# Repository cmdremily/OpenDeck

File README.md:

# OpenDeck
An open hardware/source 32-key (4x8) macro keypad based on QMK firmware.

# What it looks like?

# BOM
- **READ THE FULL INSTRUCTIONS BEFORE ORDERING PARTS OR BEGINNING ASSEMBLY**
- 1x PCB including all components from the BOM in the `hardware` folder. It's a good idea to get some spares as it's easy to mess up the assembly.
- 32x Cherry MX RGB compatible switches (e.g. MX1A-G1NA)
- 32x Keycaps of your choice (can be 3D printed)
- 1x 3D printed case body (see `mechanical/OpenDeck32` folder)
- 1x 3D printed switch plate (see `mechanical/OpenDeck32` folder)
- 1x 3D printed front plate (see `mechanical/OpenDeck32` folder)
- 1x 3D printed stand (see `mechanical/OpenDeck32` folder)
- 4x M3x0.5 15mm flathead (countersunk) screws
- 1x USB micro-B cable

For assembly an AVR ISP (Incircuit Serial Programmer) is needed unless the DFU bootloader is already programmed and correct fuses are set on your ATmega32U4 (unlikely). If you don't have an AVR ISP, you can a make a make shift programmer from it but pay close attention to the wiring, you can destroy the OpenDeck PCB and/or your Arduino if you wire it wrong.

# Electrical Assembly
**CAUTION:** The following assembly steps require soldering of Surface Mount Devices (SMDs). If you're unfamiliar with SMD soldering I recommend viewing some tutorials on the topic and maybe purchasing a practice kit online. **DO NOT ATTEMPT ASSEMBLY IF YOU'RE NOT CONFIDENT WITH SMD SOLDERING, YOU ARE VERY LIKELY TO BREAK THE COMPONENTS**.

**CAUTION 2:** When hand soldering TQFP and SSOP chips (the two large ICs on the PCB) it is very easy to bridge the pins with solder (or flux, if you don't use a NO-CLEAN variety) and create a short circuit. This short circuit will most likely cause malfunction and could damage the chip, board or the device it's connected to, please carefully inspect and test each assembled board before powering it on. Flux should be used to make soldering easier of these components and to produce better solder joints. However note that some fluxes are electrically conductive and chemically corrosive and must be thoroughly washed off the board using isopropyl alcohol, carefull scrubbing with a toothbrush and wiping off with a tissue or disposable cloth.

## Tools needed:

- Soldering Iron with sponge or brass wool for cleaning the tip
- Thin soldering wire (much harder with thick solder but doable)
- ESD and heat safe tweezers, I recommend getting a pair of titanium tweezers
- Flux
- Isopropyl Alcohol
- Magnifying glass or microscope
- Multimeter
- AVR ISP (you can make one out of an [Arduino board and some jumper wires](https://www.arduino.cc/en/Tutorial/ArduinoISP) if you don't have one)
- Steady hands and lots of patience

## (Partial) PCB Assembly
**Note**: The crystal and two adjacent load capacitances are not strictly needed. The board will function just fine from the onboard RC oscillator of the ATmega32U4, the footprints are provided as an alternative clock source should the internal RC oscillator not be good enough.

**CAUTION**: Use an anti-static wrist band when assembling, ESD can damage the components during handling.

1. Read the full instructions before proceeding
1. Solder the ICs (ATmega32U4, IS31FL3731, USBLC6, SI2323DS) on the front side of the PCB
1. Solder the Surface Mount Device (SMD) caps, resistors, fuses and the power LED on the front of PCB, pay close attention to the orientation of any LEDs and Diodes. **DO NOT SOLDER** the RGB LEDs or the diodes of the keymatrix yet, we will verify that the assembly of the hard parts is correct befor soldering these components.
1. Good job, take a break, grab a coffee.
1. Solder the through hole components **EXCEPT** the key switches, they need to be mounted to the switch plate before soldering and the board must pass electrical testing before we solder them.
1. Solder the back side SMD components. 
1. Everything except the RGB LEDs, Switches and Diodes of the keymatrix should now be soldered.
1. Clean up the board with generous amounts of isopropyl alcohol, gentle scrubbing with a toothbrush (try to reach in between the IC legs with the bristles) and wiping off the excess with clean tissues. You can check if you have gotten all the flux residue off the board by adding more isopropyl alcohol and and scrubbing carefully but thoroughly with the toothbrush, if the isopropyl alcohol evaporates without leaving a visible stain on the PCB, it is clean (the stain is flux residue).

## Electrical Verification (Part 1)

1. Optically inspect all the pins of the ATmega32U4, IS31FL3731 and USBLC6 for solder bridges. The bridges can appear between the pad, or the legs of the IC. They can be hard to see, use good lighting and a magnifying glass or microscope to inspect.
1. Using a multimeter in resistance mode at the 100k Ohm range, put the common ground probe of the multimeter onto the ground pin on the 6 pin header and the positive probe onto VCC on the 6 pin header, you should read somewhere around 30k-60k ohm resistance initially.
   - If you read significantly lower resistance, check the board for flux residue and/or solder bridges.
   - If you read significantly higher resistance, check the board for bad solder joints and connections and if you damaged any traces during assembly.
1. Do the same thing for the power and ground pin on the USB header.
1. Turn the multimeter to continuity testing mode. Place the common ground probe on the right leg (towards the ATmega32U4) of the LED next to the ATmega32U4 and the positive probe on the other leg. The LED should light up ever so slightly if it has the correct orientation.
   - If the LED doesn't light up, test on another (not soldered) LED, if it lights up in either orientation then the one on the PCB is oriented the wrong way, desolder and reorient it properly.
1. Verify that D65 is oriented with the line on the diode facing towards the right (IMPORTANT!)
1. The board is safe to power on. 

## Firmware install

**NOTE: You're going to plug in a home made device into your potentially expensive PC, we have taken all reasonable precautions and the USB spec is fairly resilient to misbehaving devices but there is still a small risk of damage to your PC. Proceed at your own risk, you have been warned.**

**NOTE: In case there was an assembly error which we did not detect with the prior testing, the USB host controller on the connected PC may enter a fault protection mode where it shuts down the entire controller (or parts of it) this will cause devices connected to it (mice, keyboards etc) to stop working. Don't be alarmed, the controller should reset after a hard power cycle of the PC.**

1. We need to program the fuses on the chip properly, using [`avrdude`](https://www.nongnu.org/avrdude/). The fuse bits that should be burned can be passed to `avrdude` as `-U lfuse:w:0x62:m -U hfuse:w:0xd9:m -U efuse:w:0xf3:m` after having selected your ISP type, baud rate, port and the correct MCU type with `-p m32u4`.
   - TBD: Add example invocation for AVR ISP under linux
1. Download the [Atmel DFU bootloader for mega chips](http://ww1.microchip.com/downloads/en/DeviceDoc/megaUSB_DFU_Bootloaders.zip) onto your hard drive and exctract the bootloader for the ATmega32U4.
1. Using `avrdude` flash the bootloader onto the ATmega32U4. 
1. Clone https://github.com/cmdremily/qmk_firmware and `cd` into the directory.
1. [Install QMK toolbox](https://beta.docs.qmk.fm/cli/cli), we only need the DFU programmer, you can ignore warings about other programmers not being found.
   - Select the cloned repo as your `QMK_HOME`.
1. [Configure QMK toolbox](https://beta.docs.qmk.fm/cli/cli_configuration), select keyboard `opendeck/32/rev1` and keymap `default`.
1. [Compile and Flash](https://beta.docs.qmk.fm/cli/cli_commands) the built firmware onte the ATmega32U4 using the DFU (USB) bootloader/programmer.

## Electrical Verification (Part 2)

Now that the board has a firmware on it we can check that the pins driving the key matrix are not shorted.

1. Connect the PCB using USB to your PCB
1. Load up a keylogger that supports the F13 to F24 keys.
1. Using a jumper wire, we're going to short some pads on the PCB to simulate key presses. 
   - For every swich there is a left and a right through hole pad (the right slightly higher up on the PCB) and a SMD diode with two pads above it.
   - For every switch, short the right upper through hole pad to the right upper leg of the corresponding SMD diode pad, your keylogger should record a keypress as F13-F24 possibly with some modifier (shift/control).
   - Repeat for each switch to see that they are all working.
   - Pay attention to spurious key-presses or unreliable behaviour, both can indicate short circuits that need to be resolved by reflowing joints to remove bridges or by cleaning out flux residue.
 1. If all the keys work proceed to the next stage.

## (partial) PCB assembly and verification Part 2

1. Solder all the remaining SMD components. Each of the diodes and RGB diodes have an orientation that must be respected when assembling.
   - To verify that the RGB diode is correctly oriented, take your multimeter in continuity testing mode, place the positive lead on the bottom left pin of the RGB LED and the common ground lead on any other pin, you should see one of the LEDs light up slightly, if not, rotate the LED.
   - Note that the colours of the LED may not be what you expect due to the low burden voltage of the multimeter. In particular the blue may appear red. Don't worry about this for now, we only need to worry about them lighting up at all which shows us the correct orientation.
   - The diodes should have a line marking on them, this line must face the marking on the PCB (to the right).
   - The RGB diodes' legs are small and close together, they are very easy to shord, please be careful and pay close attention to the solder.
1. Follow the procedure from above to clean up any flux residue from the board.
1. Optically inspect the solder joints for shorts and bridges.
1. Plug into PC, you should now see RCB puke on the key matrix.
1. Validate that all three LEDs are working on all switches.
1. Using the same jumper and keylogger from before, short the switch legs (left and right pad of the swich now, instead of the diode) to test that each diode is oriented correctly. Doing repairs after we have soldered the switches will be extremely hard due to the switch plate not allowing access without desoldering ALL switches. **PLEASE DO NOT SKIP THIS VERIFICATION STEP**.

# Final Assembly
0. Clip all switches to the switch plate, mind the orientation of the plate and the switches with respect to the PCB
0. Attach the PCB and the switchplate with the switches, make sure that the 6 pin header next to the reset push button on the PCB is inside of the opening on the bottom of the switch plate
0. Once certain that everything is correctly attached, solder the switches from the back of the PCB
0. Place the PCB and switch plate assembly in the case body, pay close attention to the USB connector's opening
0. Add the front plate on top, pay attention to orientation and screw together the assembly from the bottom using the M3x0.5 15mm screws, note that the screws are self tapping and you will encounter some resistance. Do not screw in too fast to avoid deforming the threads.
   - Note that the front cover, switch plate and case will "sandwitch" the PCB to hold it in place and the two bottom screws will go through the mounting holes in the PCB.
0. Attach keycaps
0. Plug in.
0. Place on stand and enjoy.

# Use
The keys are programmed to send F13-F24 with various combinations of modifiers (shift + control) by default. You can modify the firmware to send different key combinations or whatever you'd please by changing the source code in `keyboards/opendeck/32/` to your liking. Instructions for that can be found in the QMK documentation. You can also set specific RGB colour per key etc.

The device will appear as a regular USB keyboard to your computer.

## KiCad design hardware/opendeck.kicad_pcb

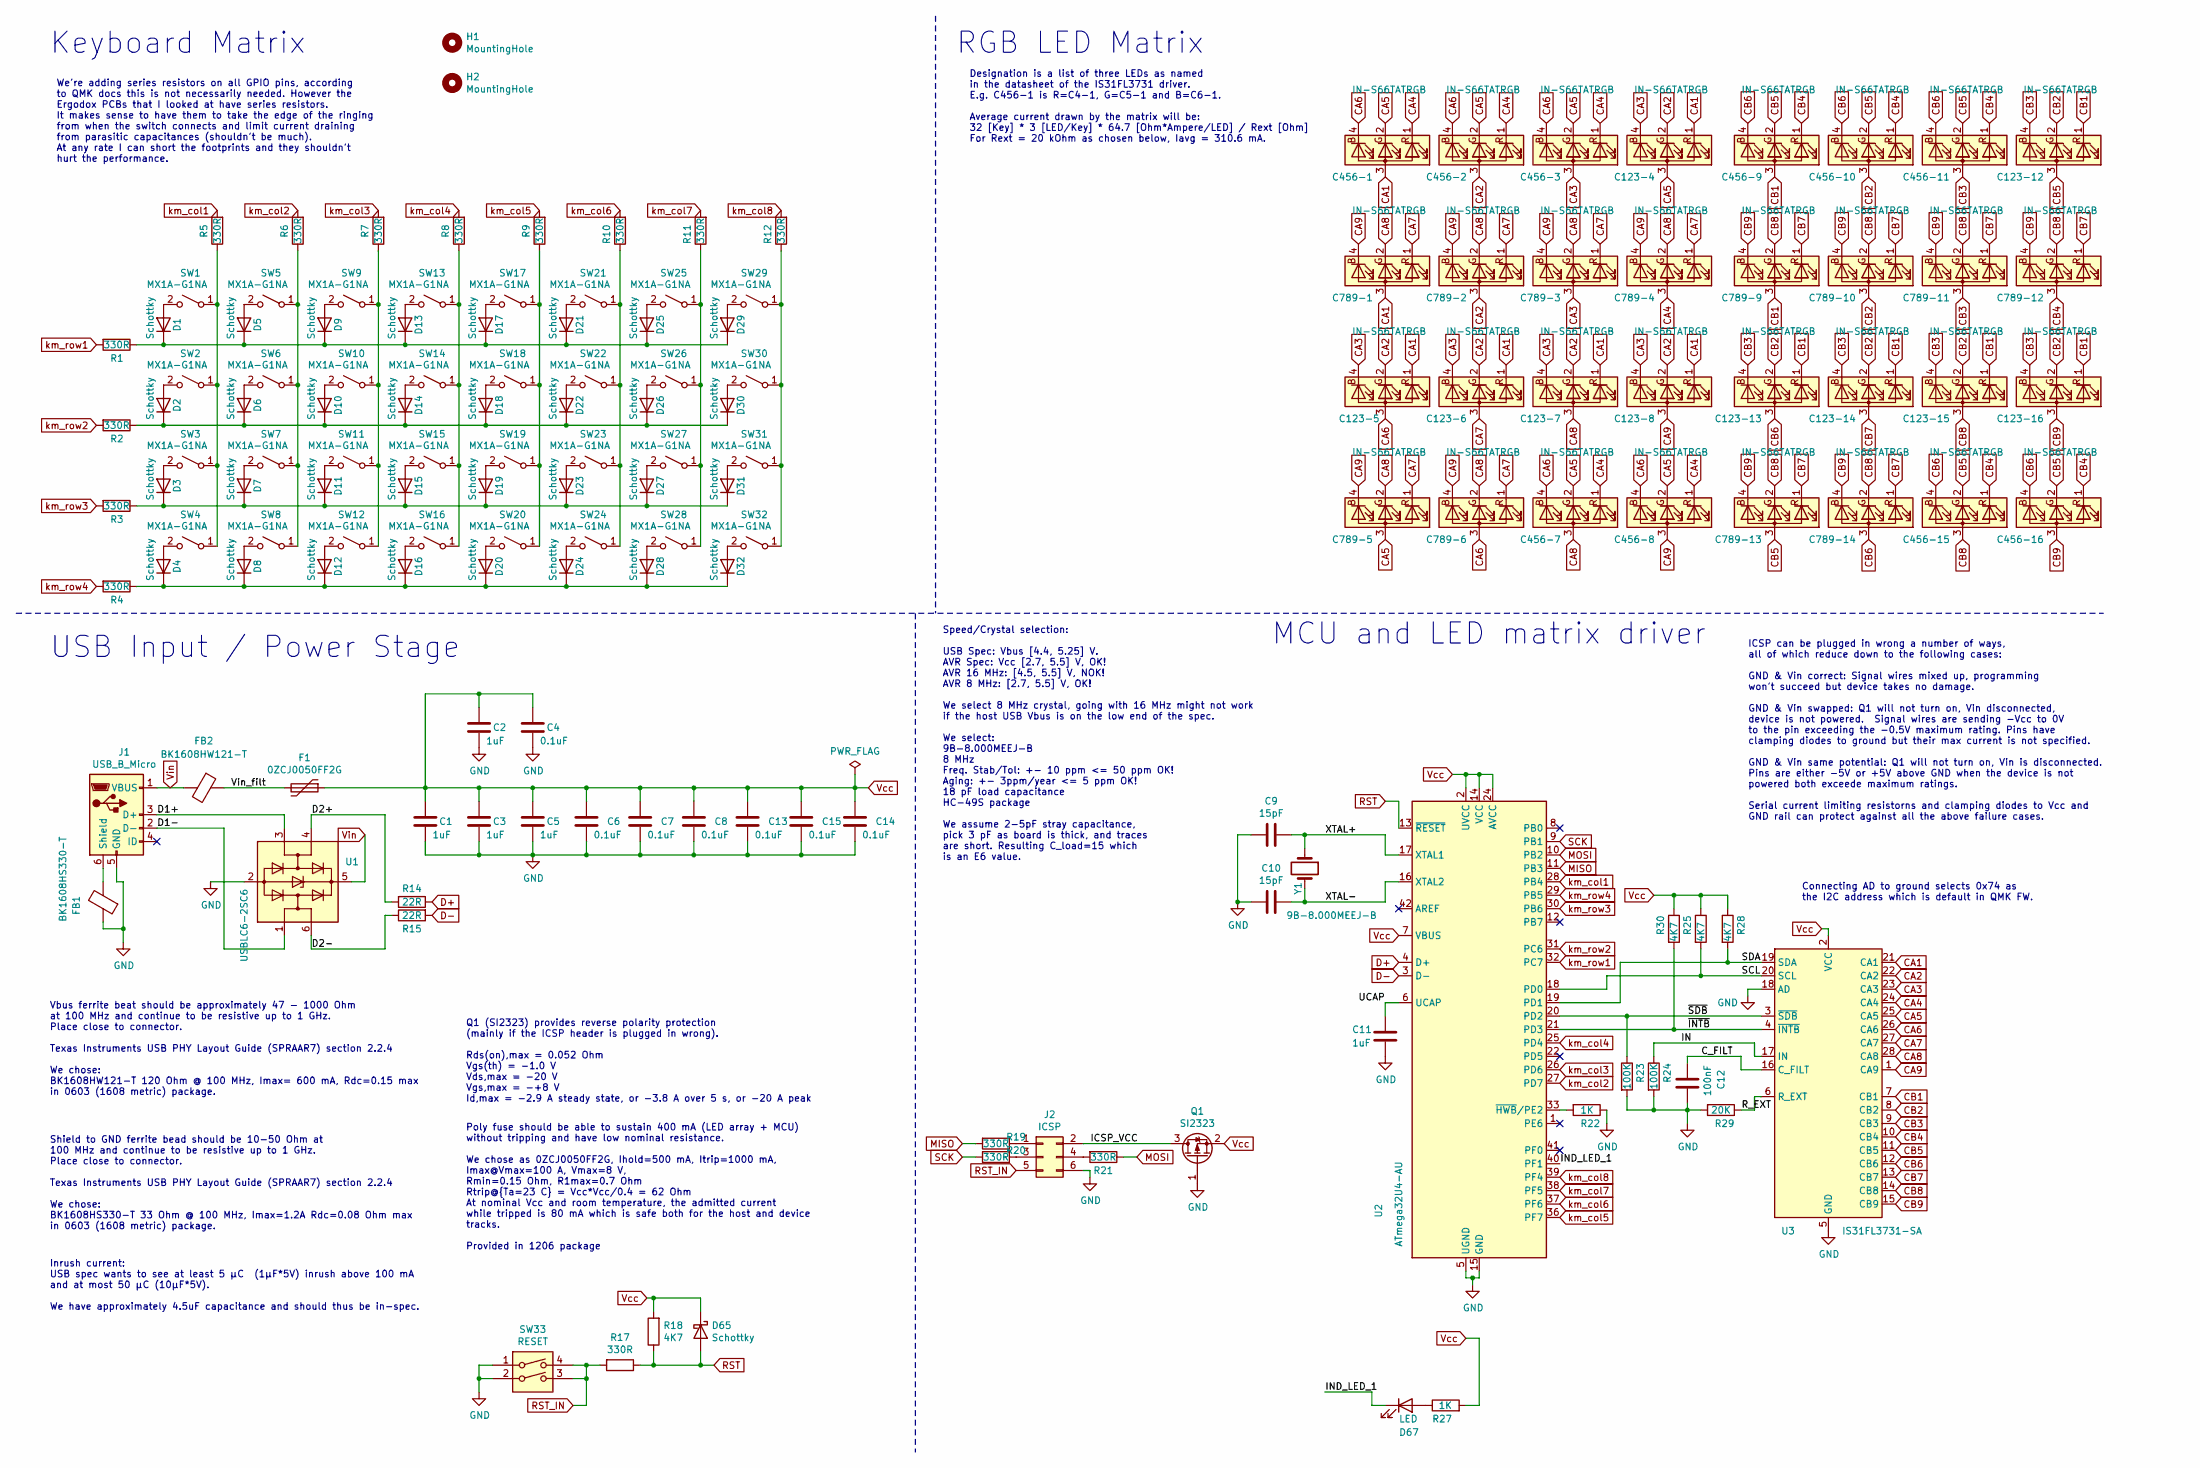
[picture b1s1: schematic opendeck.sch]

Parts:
C1, C2, C3, C5, C11: 1uF; C_0603_1608Metric
C4, C6, C7, C8, C13, C14, C15: 0.1uF; C_0603_1608Metric
C9, C10: 15pF; C_0603_1608Metric
C12: 100nF; C_0603_1608Metric
C123-4, C123-5, C123-6, C123-7, C123-8, C123-12, C123-13, C123-14, C123-15, C123-16, C456-1, C456-2, C456-3, C456-7, C456-8, C456-9, C456-10, C456-11, C456-15, C456-16, C789-1, C789-2, C789-3, C789-4, C789-5, C789-6, C789-9, C789-10, C789-11, C789-12, C789-13, C789-14: IN-S66TATRGB; RGB_LED_0606_1.6x1.5mm
D1, D2, D3, D4, D5, D6, D7, D8, D9, D10, D11, D12, D13, D14, D15, D16, D17, D18, D19, D20, D21, D22, D23, D24, D25, D26, D27, D28, D29, D30, D31, D32, D65: Schottky; D_SOD-123
D67: LED; D_0603_1608Metric
F1: 0ZCJ0050FF2G; Fuse_1206_3216Metric
FB1: BK1608HS330-T; L_0603_1608Metric
FB2: BK1608HW121-T; L_0603_1608Metric
H1, H2: MountingHole; MountingHole_4mm
J1: USB_B_Micro; USB_Micro-B_Molex-105017-0001
J2: ICSP; PinHeader_2x03_P2.54mm_Vertical
Q1: SI2323; SOT-23-Power
R1, R2, R3, R4, R5, R6, R7, R8, R9, R10, R11, R12, R17, R19, R20, R21: 330R; R_0603_1608Metric
R14, R15: 22R; R_0603_1608Metric
R18, R25, R28, R30: 4K7; R_0603_1608Metric
R22, R27: 1K; R_0603_1608Metric
R23, R24: 100K; R_0603_1608Metric
R29: 20K; R_0603_1608Metric
SW1, SW2, SW3, SW4, SW5, SW6, SW7, SW8, SW9, SW10, SW11, SW12, SW13, SW14, SW15, SW16, SW17, SW18, SW19, SW20, SW21, SW22, SW23, SW24, SW25, SW26, SW27, SW28, SW29, SW30, SW31, SW32: MX1A-G1NA; SW_Cherry_MX_1.00u_PCB
SW33: RESET; SW_TH_Tactile_Omron_B3F-10xx
U1: USBLC6-2SC6; SOT-23-6
U2: ATmega32U4-AU; TQFP-44_10x10mm_P0.8mm
U3: IS31FL3731-SA; SSOP-28_5.3x10.2mm_P0.65mm
Y1: 9B-8.000MEEJ-B; Crystal_HC49-U_Vertical

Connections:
/C_FILT: C12.1, U3.16 (C_FILT)
/D1+: J1.3 (D+), U1.3 (I/O2)
/D1-: J1.2 (D-), U1.1 (I/O1)
/D2+: R14.2, U1.4 (I/O2)
/D2-: R15.1, U1.6 (I/O1)
/ICSP_VCC: J2.2, Q1.3 (D)
/IN: R24.1, U3.17 (IN)
/IND_LED_1: D67.1 (K), U2.40 (PF1)
/R_EXT: R29.1, U3.6 (R_EXT)
/SCL: R25.2, U2.18 (PD0), U3.20 (SCL)
/SDA: R28.2, U2.19 (PD1), U3.19 (SDA)
/UCAP: C11.1, U2.6 (UCAP)
/Vin_filt: F1.2, FB2.1
/XTAL+: C9.1, U2.17 (XTAL1), Y1.1
/XTAL-: C10.1, U2.16 (XTAL2), Y1.2
/~INTB: R30.2, U2.21 (PD3), U3.4 (~INTB)
/~SDB: R23.1, U2.20 (PD2), U3.3 (~SDB)
CA1: C123-4.1, C123-5.1, C123-6.1, C123-7.1, C123-8.1, C456-1.3, C789-1.3, U3.21 (CA1)
CA2: C123-4.2, C123-5.2, C123-6.2, C123-7.2, C123-8.2, C456-2.3, C789-2.3, U3.22 (CA2)
CA3: C123-4.4, C123-5.4, C123-6.4, C123-7.4, C123-8.4, C456-3.3, C789-3.3, U3.23 (CA3)
CA4: C456-1.1, C456-2.1, C456-3.1, C456-7.1, C456-8.1, C789-4.3, U3.24 (CA4)
CA5: C123-4.3, C456-1.2, C456-2.2, C456-3.2, C456-7.2, C456-8.2, C789-5.3, U3.25 (CA5)
CA6: C123-5.3, C456-1.4, C456-2.4, C456-3.4, C456-7.4, C456-8.4, C789-6.3, U3.26 (CA6)
CA7: C123-6.3, C789-1.1, C789-2.1, C789-3.1, C789-4.1, C789-5.1, C789-6.1, U3.27 (CA7)
CA8: C123-7.3, C456-7.3, C789-1.2, C789-2.2, C789-3.2, C789-4.2, C789-5.2, C789-6.2, U3.28 (CA8)
CA9: C123-8.3, C456-8.3, C789-1.4, C789-2.4, C789-3.4, C789-4.4, C789-5.4, C789-6.4, U3.1 (CA9)
CB1: C123-12.1, C123-13.1, C123-14.1, C123-15.1, C123-16.1, C456-9.3, C789-9.3, U3.7 (CB1)
CB2: C123-12.2, C123-13.2, C123-14.2, C123-15.2, C123-16.2, C456-10.3, C789-10.3, U3.8 (CB2)
CB3: C123-12.4, C123-13.4, C123-14.4, C123-15.4, C123-16.4, C456-11.3, C789-11.3, U3.9 (CB3)
CB4: C456-9.1, C456-10.1, C456-11.1, C456-15.1, C456-16.1, C789-12.3, U3.10 (CB4)
CB5: C123-12.3, C456-9.2, C456-10.2, C456-11.2, C456-15.2, C456-16.2, C789-13.3, U3.11 (CB5)
CB6: C123-13.3, C456-9.4, C456-10.4, C456-11.4, C456-15.4, C456-16.4, C789-14.3, U3.12 (CB6)
CB7: C123-14.3, C789-9.1, C789-10.1, C789-11.1, C789-12.1, C789-13.1, C789-14.1, U3.13 (CB7)
CB8: C123-15.3, C456-15.3, C789-9.2, C789-10.2, C789-11.2, C789-12.2, C789-13.2, C789-14.2, U3.14 (CB8)
CB9: C123-16.3, C456-16.3, C789-9.4, C789-10.4, C789-11.4, C789-12.4, C789-13.4, C789-14.4, U3.15 (CB9)
D+: R14.1, U2.4 (D+)
D-: R15.2, U2.3 (D-)
GND: C1.2, C2.2, C3.2, C4.2, C5.2, C6.2, C7.2, C8.2, C9.2, C10.2, C11.2, C12.2, C13.2, C14.2, C15.2, FB1.1, J1.5 (GND), J2.6, Q1.1 (G), R22.1, R23.2, R24.2, R29.2, SW33.1, SW33.2, U1.2 (GND), U2.5 (UGND), U2.15 (GND), U2.23 (GND), U2.35 (GND), U2.43 (GND), U3.5 (GND), U3.18 (AD)
MISO: R19.2, U2.11 (PB3)
MOSI: R21.1, U2.10 (PB2)
unnamed: D1.1 (K), D5.1 (K), D9.1 (K), D13.1 (K), D17.1 (K), D21.1 (K), D25.1 (K), D29.1 (K), R1.1
unnamed: D1.2 (A), SW1.2 (B)
unnamed: D2.2 (A), SW2.2 (B)
unnamed: D3.2 (A), SW3.2 (B)
unnamed: D4.2 (A), SW4.2 (B)
unnamed: D5.2 (A), SW5.2 (B)
unnamed: D6.2 (A), SW6.2 (B)
unnamed: D7.2 (A), SW7.2 (B)
unnamed: D8.2 (A), SW8.2 (B)
unnamed: D9.2 (A), SW9.2 (B)
unnamed: D2.1 (K), D6.1 (K), D10.1 (K), D14.1 (K), D18.1 (K), D22.1 (K), D26.1 (K), D30.1 (K), R2.1
unnamed: D10.2 (A), SW10.2 (B)
unnamed: D3.1 (K), D7.1 (K), D11.1 (K), D15.1 (K), D19.1 (K), D23.1 (K), D27.1 (K), D31.1 (K), R3.1
unnamed: D11.2 (A), SW11.2 (B)
unnamed: D4.1 (K), D8.1 (K), D12.1 (K), D16.1 (K), D20.1 (K), D24.1 (K), D28.1 (K), D32.1 (K), R4.1
unnamed: D12.2 (A), SW12.2 (B)
unnamed: D13.2 (A), SW13.2 (B)
unnamed: D14.2 (A), SW14.2 (B)
unnamed: D15.2 (A), SW15.2 (B)
unnamed: D16.2 (A), SW16.2 (B)
unnamed: D17.2 (A), SW17.2 (B)
unnamed: D18.2 (A), SW18.2 (B)
unnamed: D19.2 (A), SW19.2 (B)
unnamed: D20.2 (A), SW20.2 (B)
unnamed: D21.2 (A), SW21.2 (B)
unnamed: D22.2 (A), SW22.2 (B)
unnamed: D23.2 (A), SW23.2 (B)
unnamed: D24.2 (A), SW24.2 (B)
unnamed: D25.2 (A), SW25.2 (B)
unnamed: D26.2 (A), SW26.2 (B)
unnamed: D27.2 (A), SW27.2 (B)
unnamed: D28.2 (A), SW28.2 (B)
unnamed: D29.2 (A), SW29.2 (B)
unnamed: D30.2 (A), SW30.2 (B)
unnamed: D31.2 (A), SW31.2 (B)
unnamed: D32.2 (A), SW32.2 (B)
unnamed: D67.2 (A), R27.1
unnamed: FB1.2, J1.6 (Shield)
unnamed: J2.1, R19.1
unnamed: J2.3, R20.1
unnamed: J2.4, R21.2
unnamed: R5.1, SW1.1 (A), SW2.1 (A), SW3.1 (A), SW4.1 (A)
unnamed: R6.1, SW5.1 (A), SW6.1 (A), SW7.1 (A), SW8.1 (A)
unnamed: R7.1, SW9.1 (A), SW10.1 (A), SW11.1 (A), SW12.1 (A)
unnamed: R8.1, SW13.1 (A), SW14.1 (A), SW15.1 (A), SW16.1 (A)
unnamed: R9.1, SW17.1 (A), SW18.1 (A), SW19.1 (A), SW20.1 (A)
unnamed: R10.1, SW21.1 (A), SW22.1 (A), SW23.1 (A), SW24.1 (A)
unnamed: R11.1, SW25.1 (A), SW26.1 (A), SW27.1 (A), SW28.1 (A)
unnamed: R12.1, SW29.1 (A), SW30.1 (A), SW31.1 (A), SW32.1 (A)
unnamed: R22.2, U2.33 (~HWB~/PE2)
RST: D65.2 (A), R17.1, R18.1, U2.13 (~RESET)
RST_IN: J2.5, R17.2, SW33.3, SW33.4
SCK: R20.2, U2.9 (PB1)
Vcc: C1.1, C2.1, C3.1, C4.1, C5.1, C6.1, C7.1, C8.1, C13.1, C14.1, C15.1, D65.1 (K), F1.1, Q1.2 (S), R18.2, R25.1, R27.2, R28.1, R30.1, U2.2 (UVCC), U2.7 (VBUS), U2.14 (VCC), U2.24 (AVCC), U2.34 (VCC), U2.44 (AVCC), U3.2 (VCC)
Vin: FB2.2, J1.1 (VBUS), U1.5 (VBUS)
km_col1: R5.2, U2.28 (PB4)
km_col2: R6.2, U2.27 (PD7)
km_col3: R7.2, U2.26 (PD6)
km_col4: R8.2, U2.25 (PD4)
km_col5: R9.2, U2.36 (PF7)
km_col6: R10.2, U2.37 (PF6)
km_col7: R11.2, U2.38 (PF5)
km_col8: R12.2, U2.39 (PF4)
km_row1: R1.2, U2.32 (PC7)
km_row2: R2.2, U2.31 (PC6)
km_row3: R3.2, U2.30 (PB6)
km_row4: R4.2, U2.29 (PB5)

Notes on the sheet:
Connecting AD to ground selects 0x74 as the I2C address which is default in QMK FW.
RGB LED Matrix
Designation is a list of three LEDs as named in the datasheet of the IS31FL3731 driver. E.g. C456-1 is R=C4-1, G=C5-1 and B=C6-1. Average current drawn by the matrix will be: 32 [Key] * 3 [LED/Key] * 64.7 [Ohm*Ampere/LED] / Rext [Ohm] For Rext = 20 kOhm as chosen below, Iavg = 310.6 mA.
Keyboard Matrix
We're adding series resistors on all GPIO pins, according to QMK docs this is not necessarily needed. However the Ergodox PCBs that I looked at have series resistors. It makes sense to have them to take the edge of the ringing from when the switch connects and limit current draining from parasitic 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
MCU and LED matrix driver
USB Input / Power Stage
Shield to GND ferrite bead should be 10-50 Ohm at 100 MHz and continue to be resistive up to 1 GHz. Place close to connector. Texas Instruments USB PHY Layout Guide (SPRAAR7) section 2.2.4 We chose: BK1608HS330-T 33 Ohm @ 100 MHz, Imax=1.2A Rdc=0.08 Ohm max in 0603 (1608 metric) package.
Vbus ferrite beat should be approximately 47 - 1000 Ohm at 100 MHz and continue to be resistive up to 1 GHz. Place close to connector. Texas Instruments USB PHY Layout Guide (SPRAAR7) section 2.2.4 We chose: BK1608HW121-T 120 Ohm @ 100 MHz, Imax= 600 mA, Rdc=0.15 max in 0603 (1608 metric) package.
Poly fuse should be able to sustain 400 mA (LED array + MCU) without tripping and have low nominal resistance. We chose as 0ZCJ0050FF2G, Ihold=500 mA, Itrip=1000 mA, Imax@Vmax=100 A, Vmax=8 V, Rmin=0.15 Ohm, R1max=0.7 Ohm Rtrip@{Ta=23 C} = Vcc*Vcc/0.4 = 62 Ohm At nominal Vcc and room temperature, t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
Q1 (SI2323) provides reverse polarity protection (mainly if the ICSP header is plugged in wrong). Rds(on),max = 0.052 Ohm Vgs(th) = -1.0 V Vds,max = -20 V Vgs,max = -+8 V Id,max = -2.9 A steady state, or -3.8 A over 5 s, or -20 A peak
ICSP can be plugged in wrong a number of ways, all of which reduce down to the following cases: GND & Vin correct: Signal wires mixed up, programming won't succeed but device takes no damage. GND & Vin swapped: Q1 will not turn on, Vin disconnected, device is not powered. Signal wires are sending -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
Inrush current: USB spec wants to see at least 5 µC (1µF*5V) inrush above 100 mA and at most 50 µC (10µF*5V). We have approximately 4.5uF capacitance and should thus be in-spec.
Speed/Crystal selection: USB Spec: Vbus [4.4, 5.25] V. AVR Spec: Vcc [2.7, 5.5] V, OK! AVR 16 MHz: [4.5, 5.5] V, NOK! AVR 8 MHz: [2.7, 5.5] V, OK! We select 8 MHz crystal, going with 16 MHz might not work if the host USB Vbus is on the low end of the spec. We select: 9B-8.000MEEJ-B 8 MHz Freq. Stab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

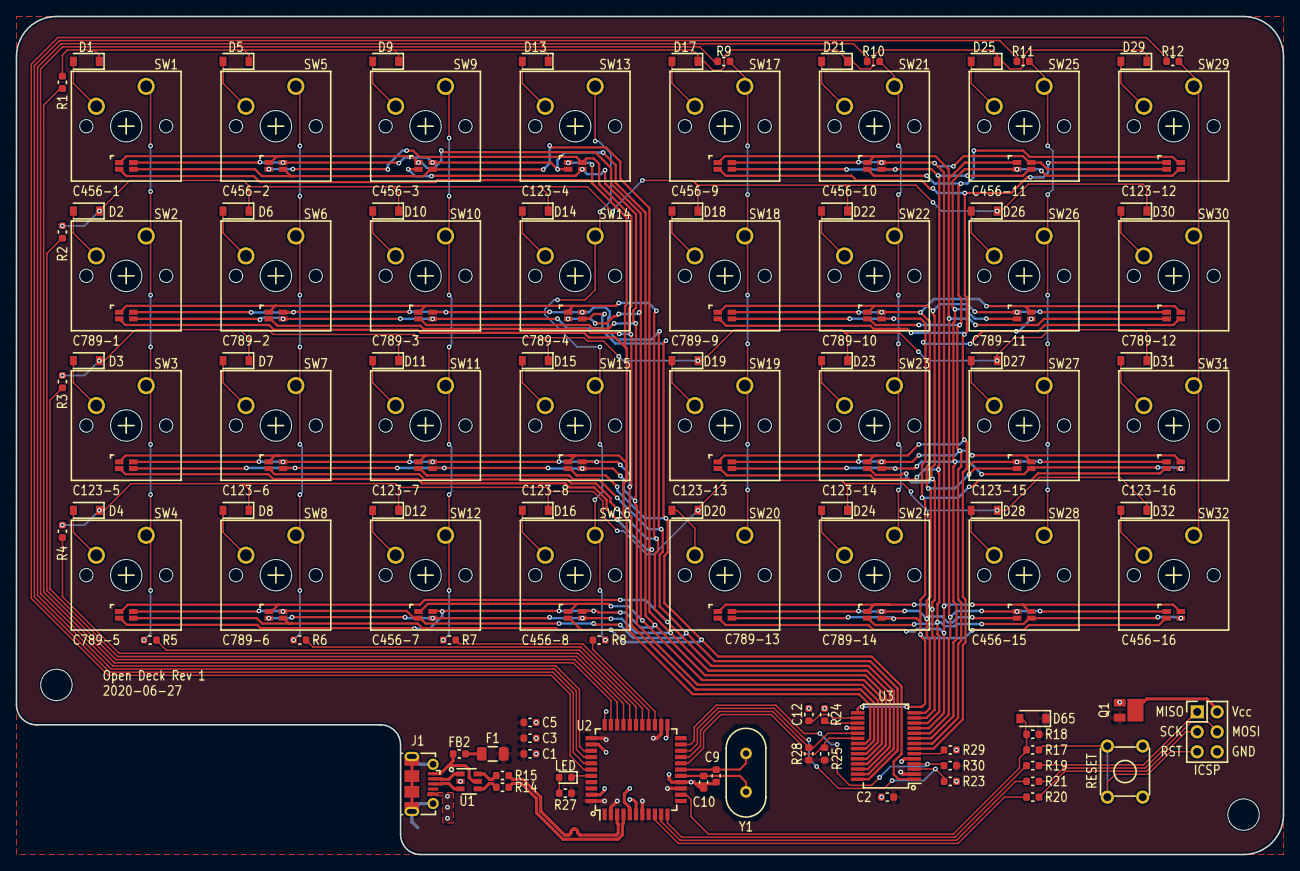
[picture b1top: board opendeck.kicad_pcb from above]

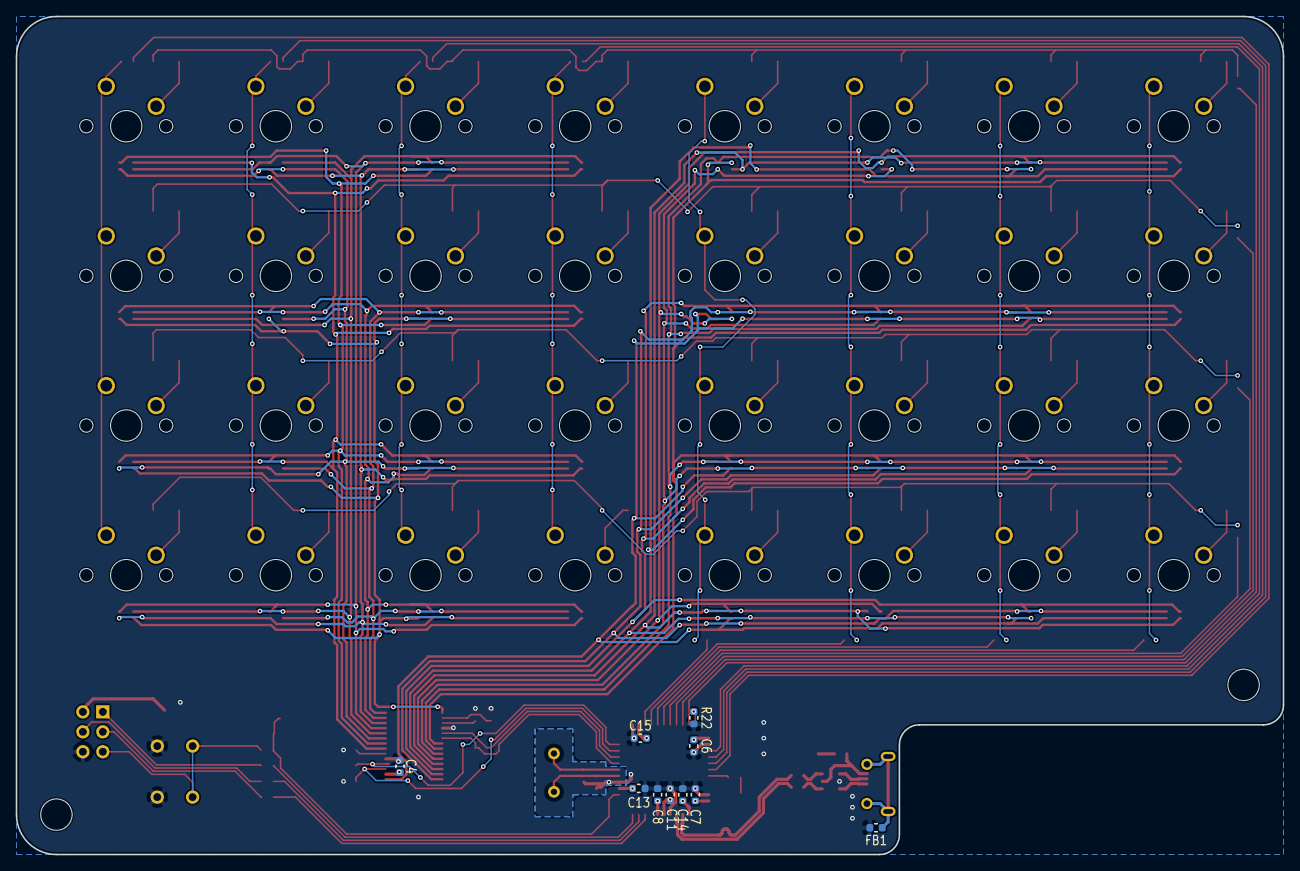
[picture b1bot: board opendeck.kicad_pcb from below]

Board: 2 copper layers, 161.3 x 106.7 mm, 153 parts (10 on the bottom side), 107 nets.

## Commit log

2020-07-18 Initial Import
2020-07-18 Add QMK firmware as sub module
2020-07-25 Cleaning up and organizing files to admit different variants of the keyboard.
2020-07-25 We should probably have a gitignore file
2021-04-24 Add images to README and some small improvements.
2021-04-24 Fix image links...
2021-04-24 Fix image links... For real this time...
